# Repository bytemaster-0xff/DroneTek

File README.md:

# DroneTek
Collection of software, hardware and design resources for the Nivek Drone Family

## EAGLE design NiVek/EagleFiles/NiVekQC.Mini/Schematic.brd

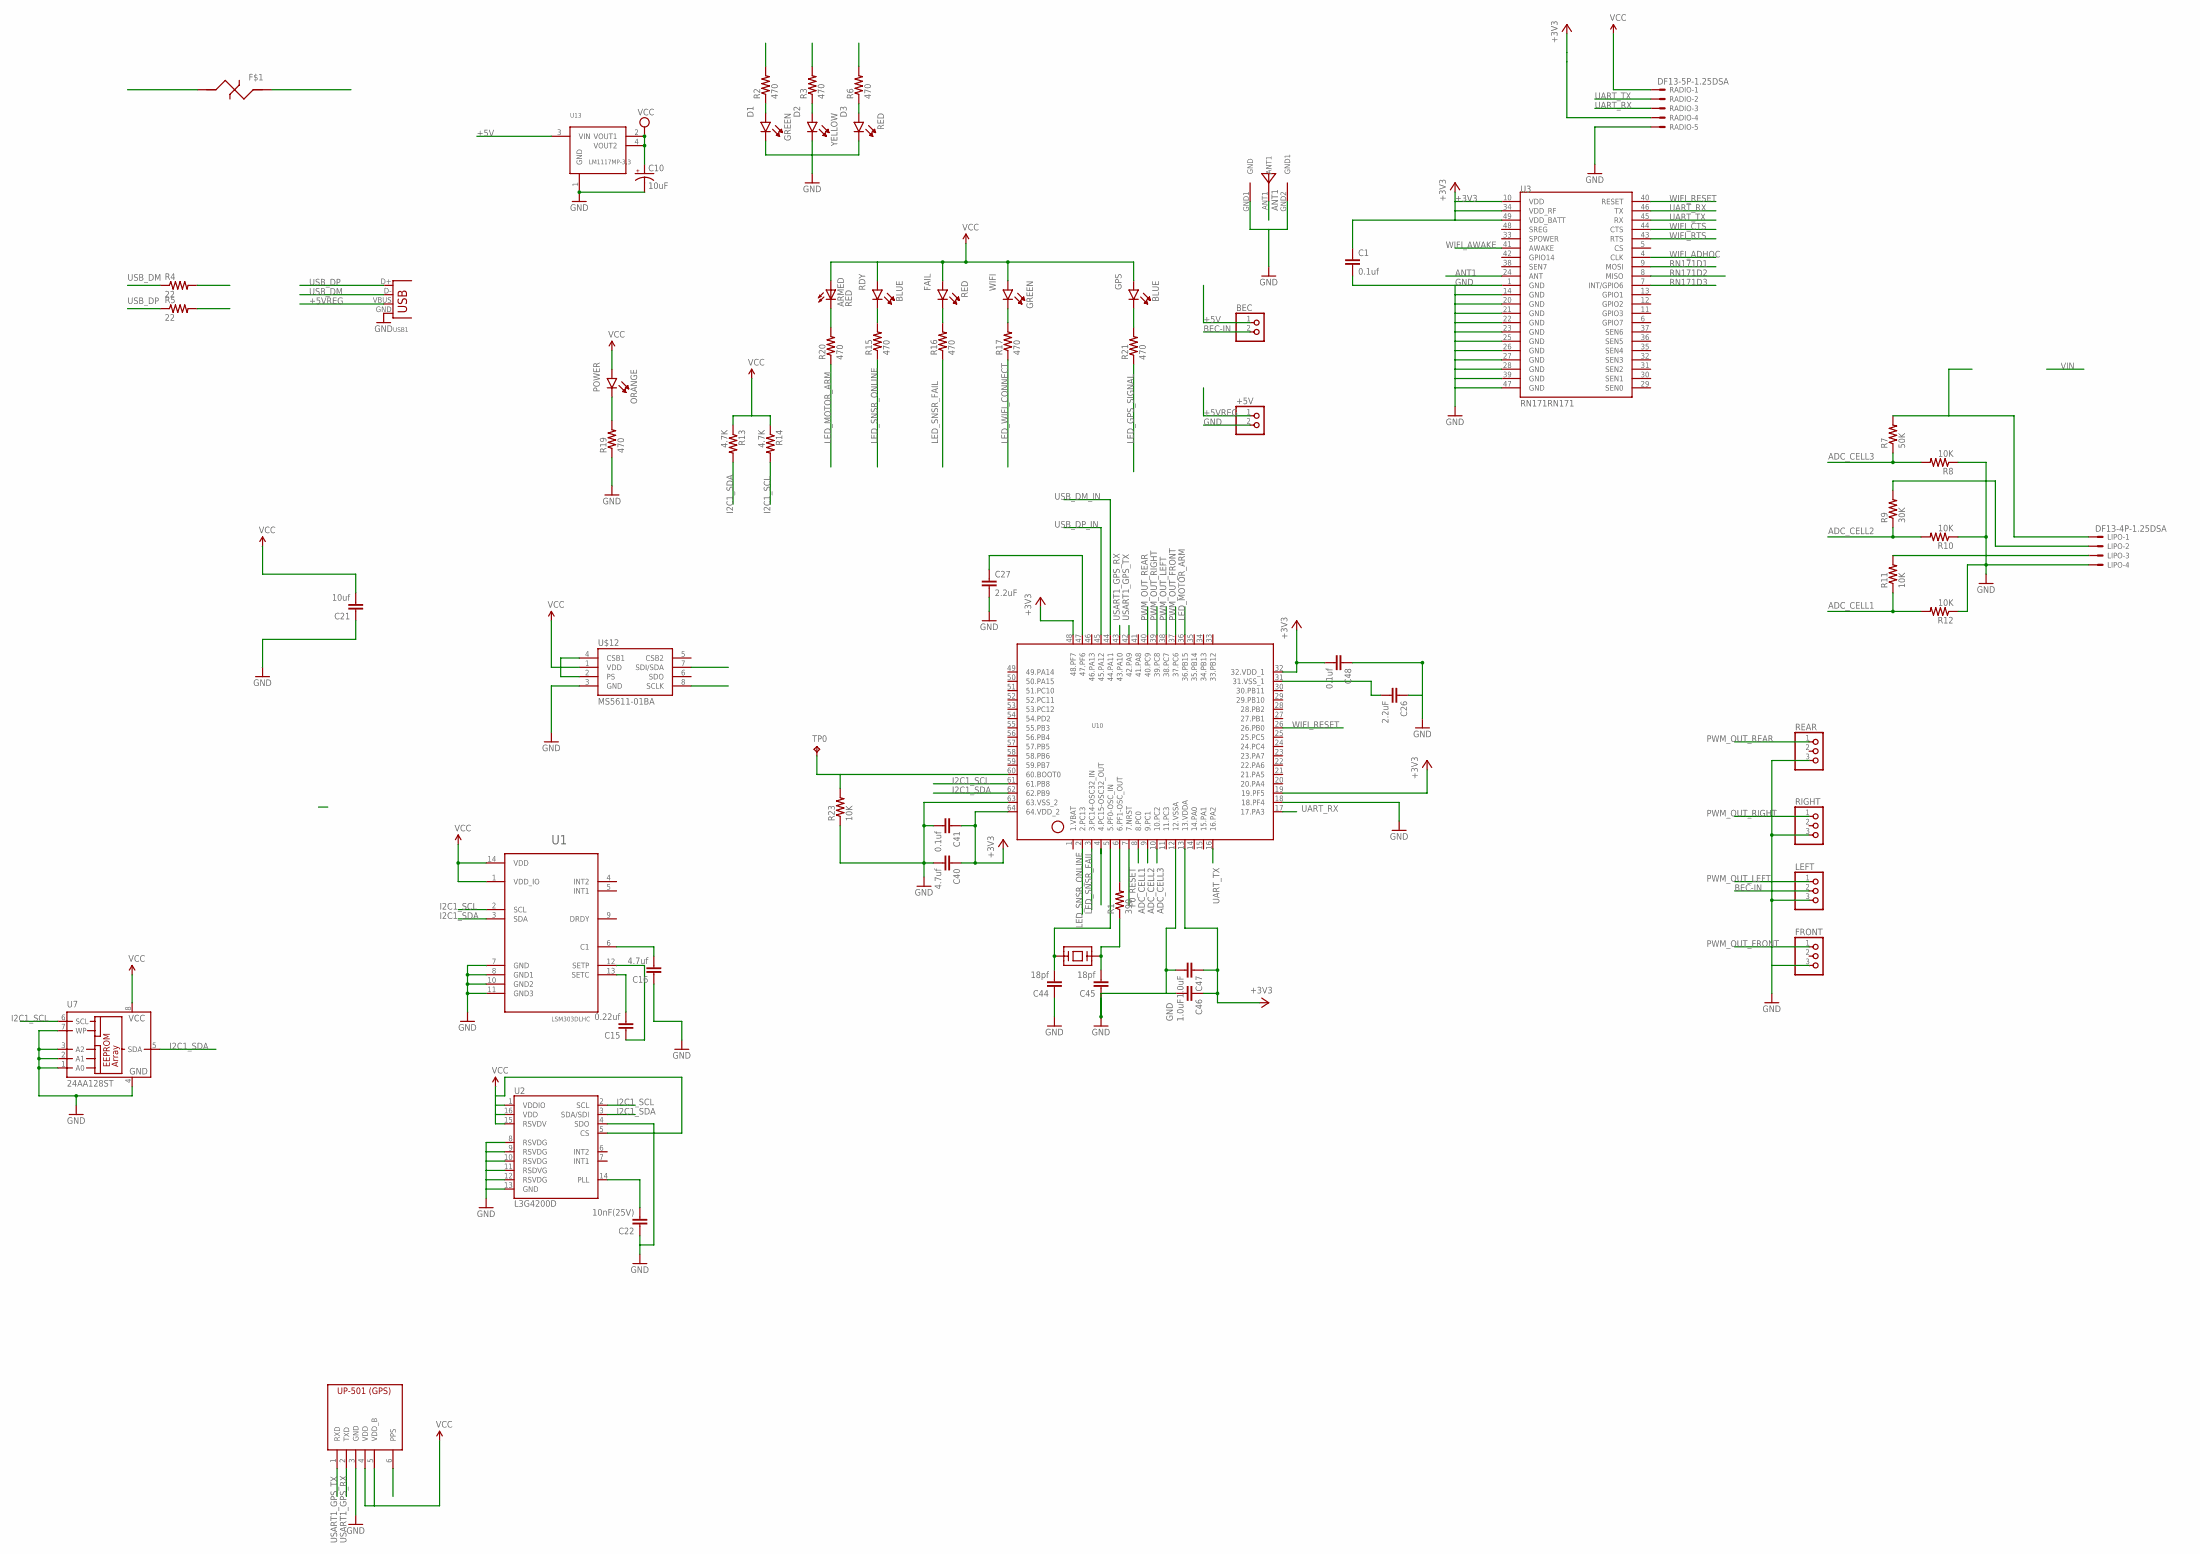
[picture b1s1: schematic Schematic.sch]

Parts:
+5V: PINHD-1X2; 1X02
ARMED: RED; LED-1206
BEC: PINHD-1X2; 1X02
C1, C41, C48: 0.1uf; 0805
C10: 10uF; CT3528
C15: 0.22uf; 0805
C16, C40: 4.7uf; 0805
C21: 10uf; 0805
C22: 10nF(25V); 0805
C26, C27: 2.2uF; 0805
C44, C45: 18pf; 0805
C46, C47: 1.0uF; 0805
D1: GREEN; LED0805
D2: YELLOW; LED0805
D3: RED; LED0805
F1: 1206L050_FUSE
FAIL: RED; LED0805
FRONT: PINHD-1X3; 1X03
GPS: BLUE; LED0805
LEFT: PINHD-1X3; 1X03
LIPO: DF13-4P-1.25DSA
POWER: ORANGE; LED0805
R1: 390; 0805
R2, R3, R6, R15, R16, R17, R19, R20, R21: 470; 0805
R4, R5: 22; 0805
R7: 50K; 0805
R8, R10, R11, R12, R23: 10K; 0805
R9: 30K; 0805
R13, R14: 4.7K; 0805
RADIO: DF13-5P-1.25DSA
RDY: BLUE; LED0805
REAR: PINHD-1X3; 1X03
RIGHT: PINHD-1X3; 1X03
TP0: TPTP15R; TP15R
U1: LSM303DLHC; LGA3X5X1-14L
U2: L3G4200D; LGA16-4X4
U3: RN171RN171; RN171
U7: 24AA128ST; TSSOP8; MPN 24AA128-I/ST
U10: STM32F051XXX; STM32F051XXX_LPFP64
U13: LM1117MP-3.3; SOT223
U$1: U.FLCONNECTOR
U$4: UP501; UP-501
U$12: MS5611-01BA
USB1: DX2R005HN2E700; USB-MB-S
WIFI: GREEN; LED0805
X2: ABRACON_ABM7; ABRACON_ABM7_CERAMIC_XTAL

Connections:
+3V3: ARMED.A, C1.1, C10.+, C21.2, C40.1, C41.1, C46.1, C47.1, C48.2, FAIL.P$1 (A), GPS.P$1 (A), POWER.P$1 (A), R13.1, R14.1, RADIO.4, RDY.P$1 (A), U1.1 (VDD_IO), U1.14 (VDD), U2.1 (VDDIO), U2.5 (CS), U2.15 (RSVDV), U2.16 (VDD), U3.10 (VDD), U3.34 (VDD_RF), U3.49 (VDD_BATT), U7.8 (VCC), U10.13 (13.VDDA), U10.19 (19.PF5), U10.32 (32.VDD_1), U10.48 (48.PF7), U10.64 (64.VDD_2), U13.2 (VOUT1), U13.4 (VOUT2), U$4.4 (VDD), U$4.5 (VDD_B), U$12.1 (VDD), U$12.2 (PS), U$12.4 (CSB1), WIFI.P$1 (A)
+5V: BEC.1, F1.P$2, RADIO.1, U13.3 (VIN)
+5VREG: +5V.1, F1.P$1, USB1.VBUS
ADC_CELL1: R11.1, R12.2, U10.8 (8.PC0)
ADC_CELL2: R9.1, R10.2, U10.9 (9.PC1)
ADC_CELL3: R7.1, R8.2, U10.10 (10.PC2)
ANT1: U3.24 (ANT), U$1.ANT1
BEC-IN: BEC.2, LEFT.2
F0_RESET: U10.7 (7.NRST)
GND: +5V.2, C1.2, C10.-, C16.1, C21.1, C22.1, C26.1, C27.2, C40.2, C41.2, C44.1, C45.1, C46.2, C47.2, C48.1, D1.C, D2.C, D3.C, FRONT.3, LEFT.3, LIPO.4, R8.1, R10.1, R12.1, R19.1, R23.1, RADIO.5, REAR.3, RIGHT.3, U1.7 (GND), U1.8 (GND1), U1.10 (GND2), U1.11 (GND3), U2.4 (SDO), U2.8 (RSVDG), U2.9 (RSVDG), U2.10 (RSVDG), U2.11 (RSDVG), U2.12 (RSVDG), U2.13 (GND), U3.1 (GND), U3.14 (GND), U3.20 (GND), U3.21 (GND), U3.22 (GND), U3.23 (GND), U3.25 (GND), U3.26 (GND), U3.27 (GND), U3.28 (GND), U3.39 (GND), U3.47 (GND), U7.1 (A0), U7.2 (A1), U7.3 (A2), U7.4 (GND), U7.7 (WP), U10.12 (12.VSSA), U10.18 (18.PF4), U10.63 (63.VSS_2), U13.1 (GND), U$1.GND1 (GND), U$1.GND2 (GND1), U$4.3 (GND), U$12.3 (GND), USB1.GND
I2C1_SCL: R14.2, U1.2 (SCL), U2.2 (SCL), U7.6 (SCL), U10.61 (61.PB8), U$12.8 (SCLK)
I2C1_SDA: R13.2, U1.3 (SDA), U2.3 (SDA/SDI), U7.5 (SDA), U10.62 (62.PB9), U$12.7 (SDI/SDA)
LED_GPS_SIGNAL: R21.1, U$4.6 (PPS)
LED_MOTOR_ARM: R20.1, U10.36 (36.PB15)
LED_SNSR_FAIL: R16.1, U10.3 (3.PC14-OSC32_IN)
LED_SNSR_ONLINE: R15.1, U10.2 (2.PC13)
LED_WIFI_CONNECT: R17.1, U10.4 (4.PC15-OSC32_OUT)
unnamed: D1.P$1 (A), R2.1
unnamed: D2.P$1 (A), R3.1
unnamed: R1.2, U10.6 (6.PF1-OSC_OUT)
unnamed: D3.P$1 (A), R6.1
unnamed: C16.2, U1.6 (C1)
unnamed: R15.2, RDY.C
unnamed: C15.1, U1.12 (SETP)
unnamed: C15.2, U1.13 (SETC)
unnamed: FAIL.C, R16.2
unnamed: ARMED.C, R20.2
unnamed: LIPO.3, R11.2
unnamed: LIPO.2, R9.2
unnamed: R17.2, WIFI.C
unnamed: POWER.C, R19.2
unnamed: R23.2, TP0.TP, U10.60 (60.BOOT0)
unnamed: C22.2, U2.14 (PLL)
unnamed: GPS.C, R21.2
unnamed: C26.2, U10.31 (31.VSS_1)
unnamed: C27.1, U10.47 (47.PF6)
OSC_IN: C44.2, U10.5 (5.PF0-OSC_IN), X2.P$1
OSC_OUT: C45.2, R1.1, X2.P$2
PWM_OUT_FRONT: FRONT.1, U10.37 (37.PC6)
PWM_OUT_LEFT: LEFT.1, U10.38 (38.PC7)
PWM_OUT_REAR: REAR.1, U10.40 (40.PC9)
PWM_OUT_RIGHT: RIGHT.1, U10.39 (39.PC8)
RN171D1: R2.2, U3.9 (MOSI)
RN171D2: R3.2, U3.8 (MISO)
RN171D3: R6.2, U3.7 (INT/GPIO6)
UART_RX: RADIO.3, U3.46 (TX), U10.17 (17.PA3)
UART_TX: RADIO.2, U3.45 (RX), U10.16 (16.PA2)
USART1_GPS_RX: U10.43 (43.PA10), U$4.2 (TXD)
USART1_GPS_TX: U10.42 (42.PA9), U$4.1 (RXD)
USB_DM: R4.1, USB1.D-
USB_DM_IN: R4.2, U10.44 (44.PA11)
USB_DP: R5.1, USB1.D+
USB_DP_IN: R5.2, U10.45 (45.PA12)
VIN_PROTECTED: LIPO.1, R7.2
WIFI_ADHOC: U3.4 (CLK)
WIFI_AWAKE: U3.41 (AWAKE)
WIFI_CTS: U3.44 (CTS)
WIFI_RESET: U3.40 (RESET), U10.26 (26.PB0)
WIFI_RTS: U3.43 (RTS)

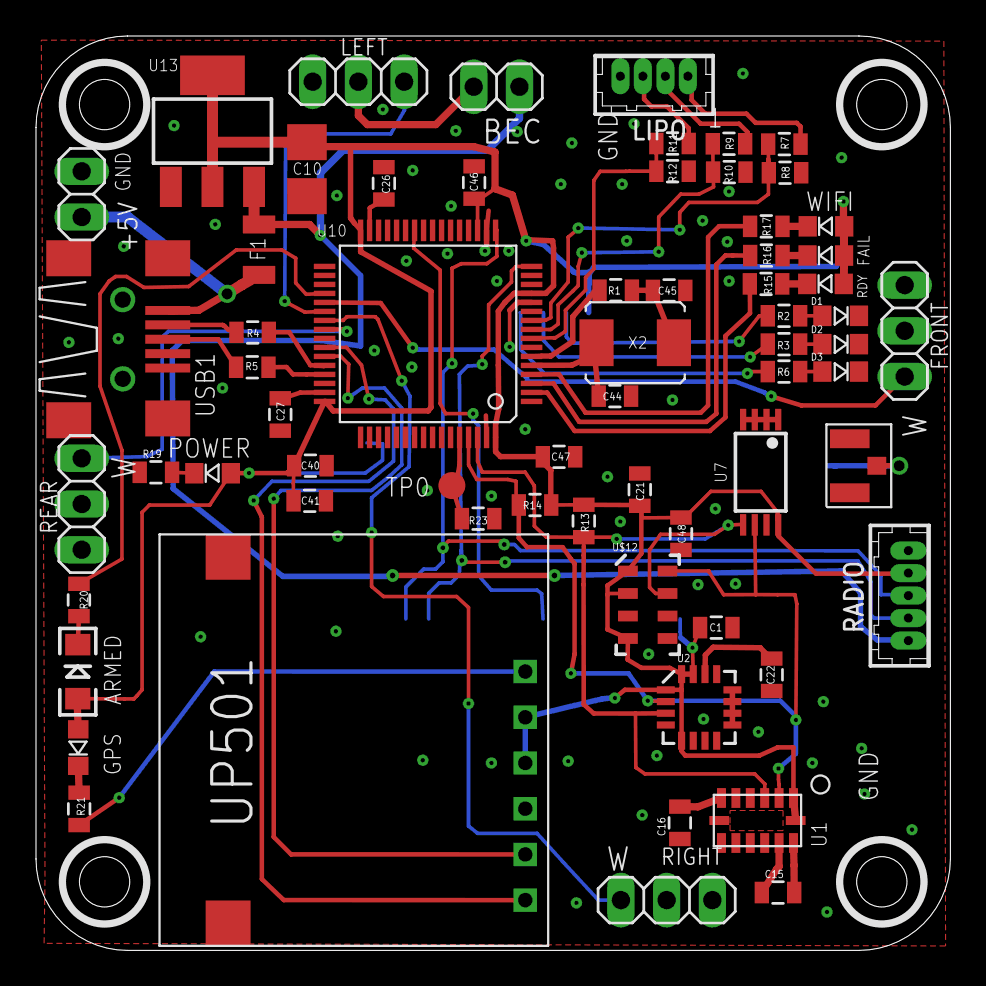
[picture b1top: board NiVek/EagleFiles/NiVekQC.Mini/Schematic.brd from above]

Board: 2 copper layers, 50.8 x 50.8 mm, 66 parts (1 on the bottom side), 54 nets.

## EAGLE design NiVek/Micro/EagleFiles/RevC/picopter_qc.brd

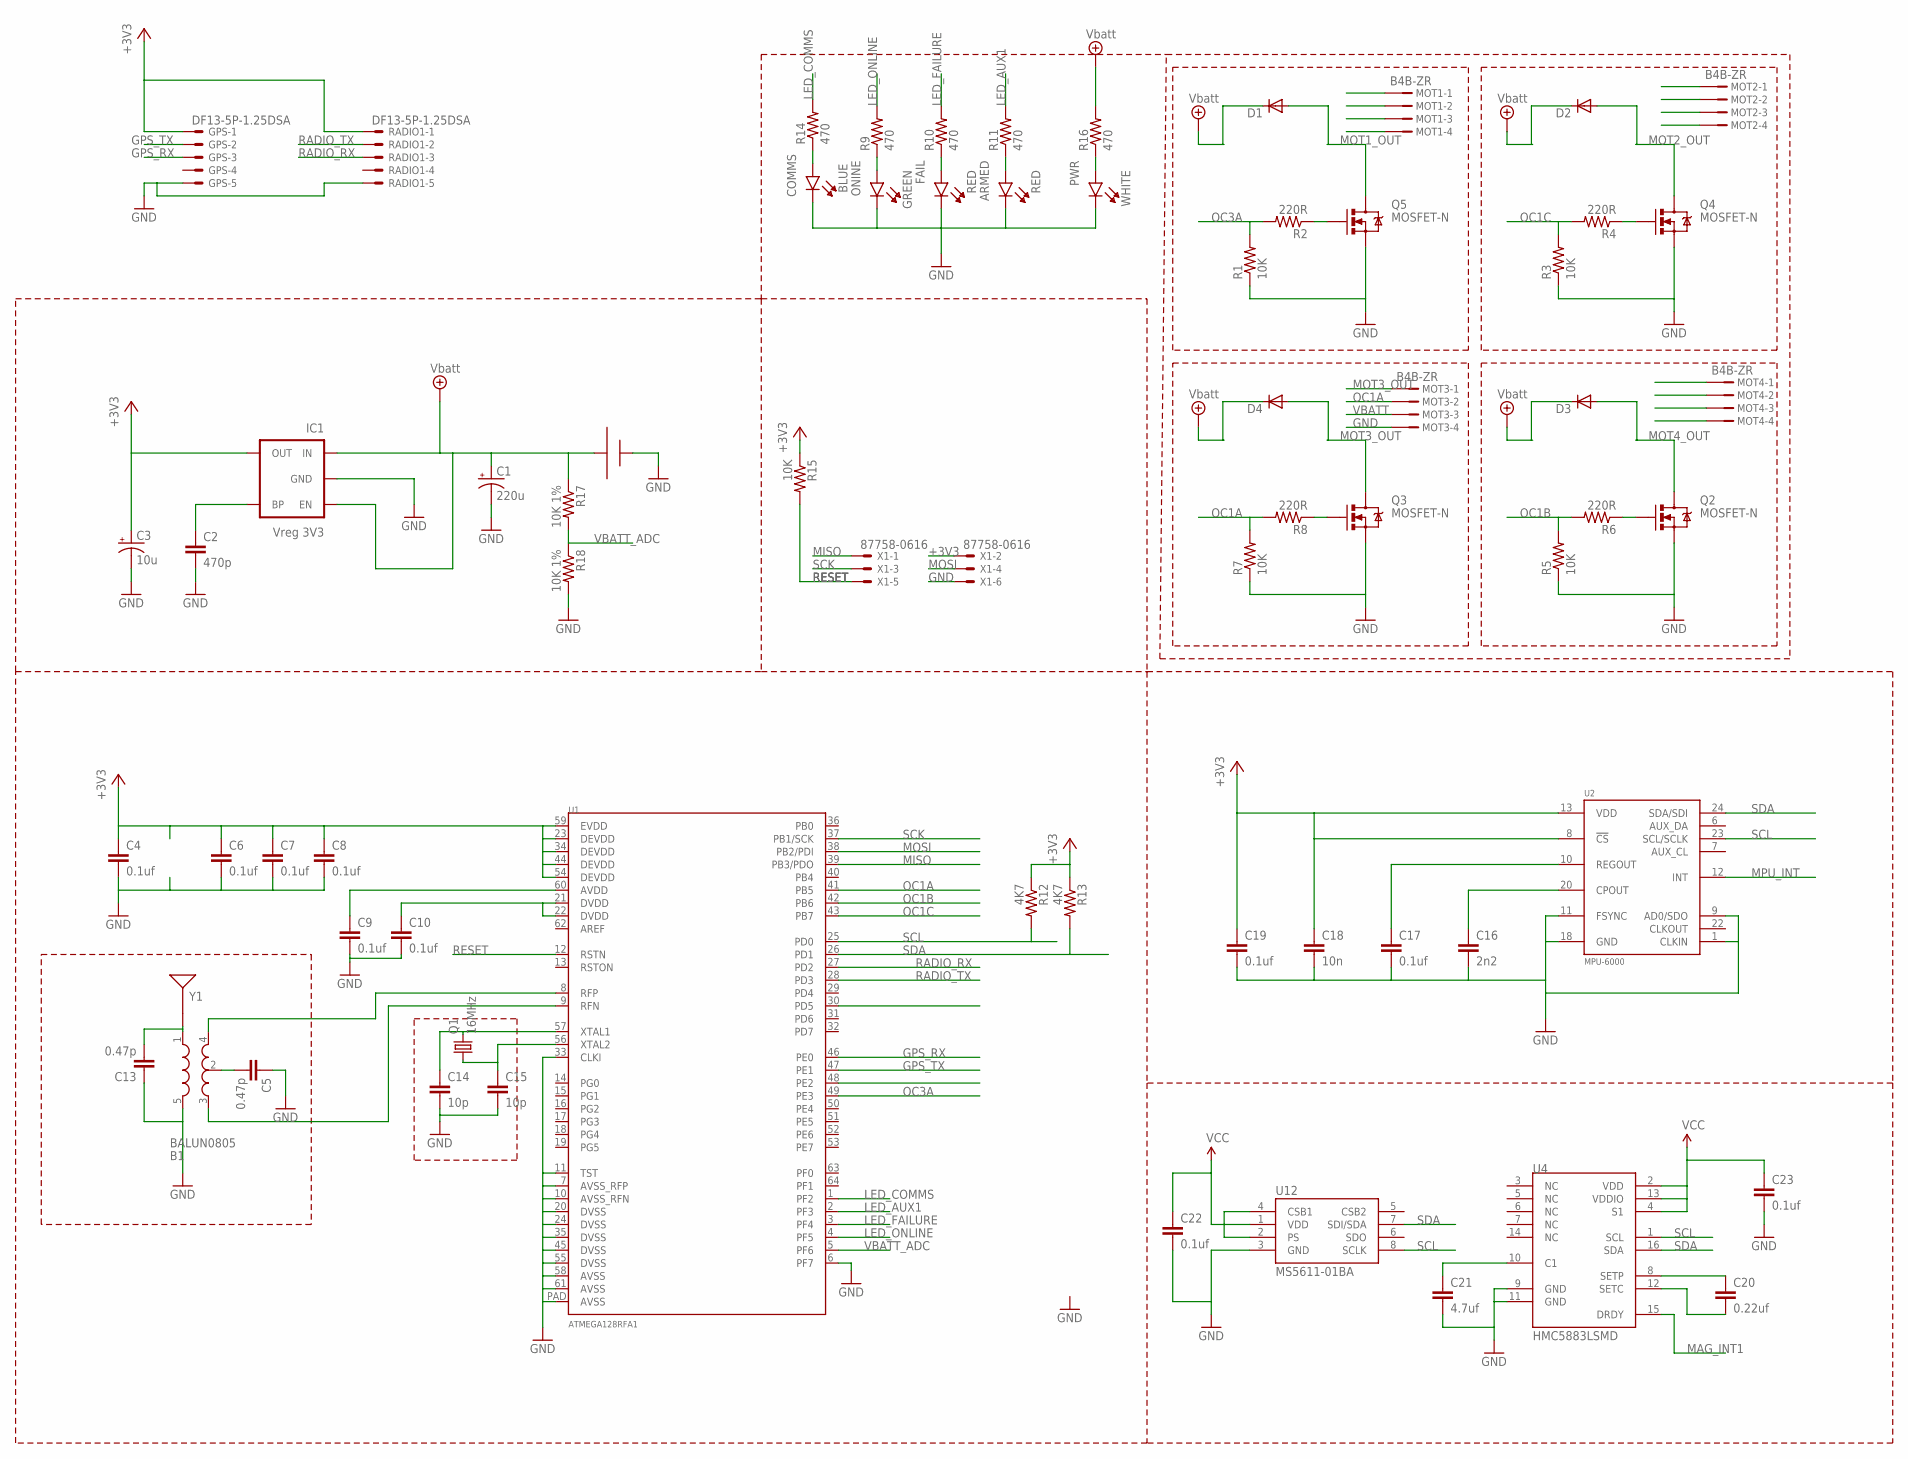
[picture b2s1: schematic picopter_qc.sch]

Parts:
ARMED: RED; LED0805
B1: BALUN0805; BALUN
BATT1: BATT-CONNJST-PH-VERT; JST-PH-2-VERT
C1: 220u; SMC_B
C2: 470p; C0603
C3: 10u; SMC_B
C4, C6, C7, C8, C9, C10, C17, C19, C22, C23: 0.1uf; C0603
C5, C13: 0.47p; C0603
C14, C15: 10p; C0603
C16: 2n2; C0603
C18: 10n; C0603
C20: 0.22uf; C0603
C21: 4.7uf; C0603
COMMS: BLUE; LED0805
D1, D2, D3, D4: DIODE-MINIMELF; MINIMELF
FAIL: RED; LED0805
GPS: DF13-5P-1.25DSA
IC1: Vreg 3V3; SOT23-5
MOT1, MOT2, MOT3, MOT4: B4B-ZR
ONINE: GREEN; LED0805
PWR: WHITE; LED0805
Q1: 16MHz; CTS406
Q2, Q3, Q4, Q5: MOSFET-N; SOT23-3
R1, R3, R5, R7, R15: 10K; R0603
R2, R4, R6, R8: 220R; R0603
R9, R10, R11, R14, R16: 470; 0805
R12, R13: 4K7; R0603
R17, R18: 10K 1%; R0603
RADIO1: DF13-5P-1.25DSA
U1: ATMEGA128RFA1; QFN-64
U2: MPU-6000; QFN-24
U4: HMC5883LSMD; 16LPCC
U12: MS5611-01BA
X1: 87758-0616
Y1: ANTENNA2SMD5; ANTENNA-CHIP5

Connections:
+3V3: C3.+, C4.1, C6.1, C7.1, C8.1, C18.1, C19.1, C22.1, C23.1, GPS.1, IC1.5 (OUT), R12.1, R13.1, R15.1, RADIO1.1, U1.23 (DEVDD), U1.34 (DEVDD), U1.44 (DEVDD), U1.54 (DEVDD), U1.59 (EVDD), U2.8 (!CS), U2.13 (VDD), U4.2 (VDD), U4.4 (S1), U4.13 (VDDIO), U12.1 (VDD), U12.2 (PS), U12.4 (CSB1), X1.2
GND: ARMED.C, B1.5 (GND), BATT1.N, C1.-, C2.2, C3.-, C4.2, C5.1, C6.2, C7.2, C8.2, C9.2, C10.2, C13.1, C14.2, C15.2, C16.2, C17.2, C18.2, C19.2, C21.2, C22.2, C23.2, COMMS.C, FAIL.C, GPS.5, IC1.2 (GND), MOT1.4, MOT2.4, MOT3.4, MOT4.4, ONINE.C, PWR.C, Q2.2 (S), Q3.2 (S), Q4.2 (S), Q5.2 (S), R1.1, R3.1, R5.1, R7.1, R18.2, RADIO1.5, U1.6 (PF7), U1.7 (AVSS_RFP), U1.10 (AVSS_RFN), U1.11 (TST), U1.20 (DVSS), U1.24 (DVSS), U1.33 (CLKI), U1.35 (DVSS), U1.45 (DVSS), U1.55 (DVSS), U1.58 (AVSS), U1.61 (AVSS), U1.PAD (AVSS), U2.1 (CLKIN), U2.9 (AD0/SDO), U2.11 (FSYNC), U2.18 (GND), U4.9 (GND), U4.11 (GND), U12.3 (GND), X1.6
GPS_RX: GPS.3, U1.46 (PE0)
GPS_TX: GPS.2, U1.47 (PE1)
LED_AUX1: R11.2, U1.2 (PF3)
LED_COMMS: R14.2, U1.1 (PF2)
LED_FAILURE: R10.2, U1.3 (PF4)
LED_ONLINE: R9.2, U1.4 (PF5)
MAG_INT1: U1.48 (PE2), U4.15 (DRDY)
MISO: U1.39 (PB3/PDO), X1.1
MOSI: U1.38 (PB2/PDI), X1.4
MOT1_OUT: D1.A, MOT1.1, Q5.3 (D)
MOT2_OUT: D2.A, MOT2.1, Q4.3 (D)
MOT3_OUT: D4.A, MOT3.1, Q3.3 (D)
MOT4_OUT: D3.A, MOT4.1, Q2.3 (D)
MPU_INT: U1.30 (PD5), U2.12 (INT)
MS1: B1.1 (IN), C13.2, Y1.FEED
unnamed: C2.1, IC1.4 (BP)
unnamed: B1.2 (GND), C5.2
unnamed: C10.1, U1.21 (DVDD), U1.22 (DVDD)
unnamed: C9.1, U1.60 (AVDD)
unnamed: B1.3 (OUT1), U1.9 (RFN)
unnamed: B1.4 (OUT2), U1.8 (RFP)
unnamed: C14.1, Q1.3 (2), U1.57 (XTAL1)
unnamed: C15.1, Q1.1, U1.56 (XTAL2)
unnamed: ONINE.P$1 (A), R9.1
unnamed: FAIL.P$1 (A), R10.1
unnamed: C20.1, U4.8 (SETP)
unnamed: C16.1, U2.20 (CPOUT)
unnamed: C17.1, U2.10 (REGOUT)
unnamed: C20.2, U4.12 (SETC)
unnamed: C21.1, U4.10 (C1)
unnamed: ARMED.P$1 (A), R11.1
unnamed: COMMS.P$1 (A), R14.1
unnamed: PWR.P$1 (A), R16.1
unnamed: Q5.1 (G), R2.1
unnamed: Q4.1 (G), R4.1
unnamed: Q2.1 (G), R6.1
unnamed: Q3.1 (G), R8.1
OC1A: MOT3.2, R7.2, R8.2, U1.41 (PB5)
OC1B: MOT4.2, R5.2, R6.2, U1.42 (PB6)
OC1C: MOT2.2, R3.2, R4.2, U1.43 (PB7)
OC3A: MOT1.2, R1.2, R2.2, U1.49 (PE3)
RADIO_RX: RADIO1.3, U1.27 (PD2)
RADIO_TX: RADIO1.2, U1.28 (PD3)
RESET: R15.2, U1.12 (RSTN), X1.5
SCK: U1.37 (PB1/SCK), X1.3
SCL: R12.2, U1.25 (PD0), U2.23 (SCL/SCLK), U4.1 (SCL), U12.8 (SCLK)
SDA: R13.2, U1.26 (PD1), U2.24 (SDA/SDI), U4.16 (SDA), U12.7 (SDI/SDA)
VBATT: BATT1.P, C1.+, D1.C, D2.C, D3.C, D4.C, IC1.1 (IN), IC1.3 (EN), MOT1.3, MOT2.3, MOT3.3, MOT4.3, R16.2, R17.1
VBATT_ADC: R17.2, R18.1, U1.5 (PF6)

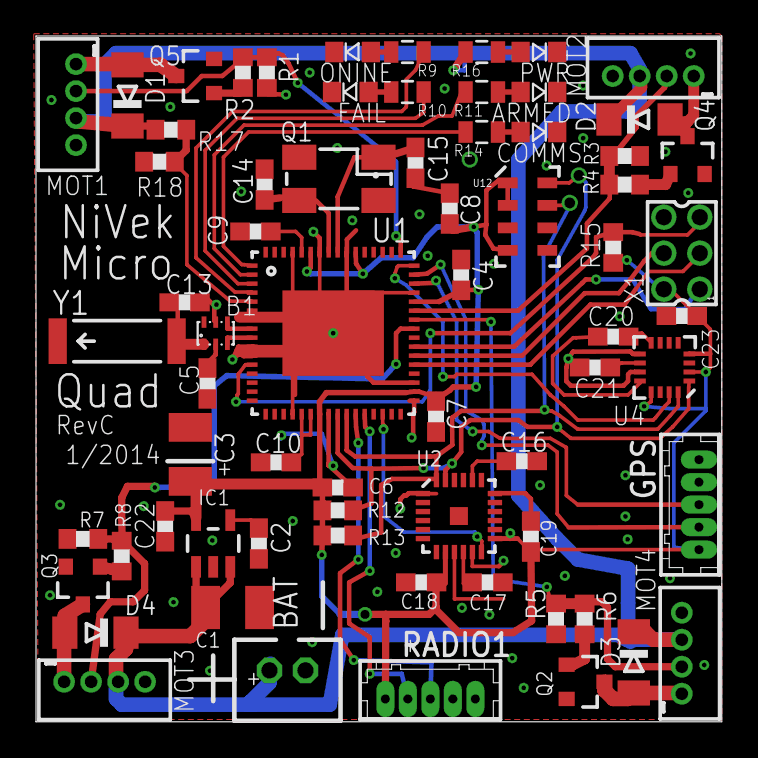
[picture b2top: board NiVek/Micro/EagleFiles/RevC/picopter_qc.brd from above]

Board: 2 copper layers, 38.1 x 38.1 mm, 68 parts (0 on the bottom side), 51 nets.

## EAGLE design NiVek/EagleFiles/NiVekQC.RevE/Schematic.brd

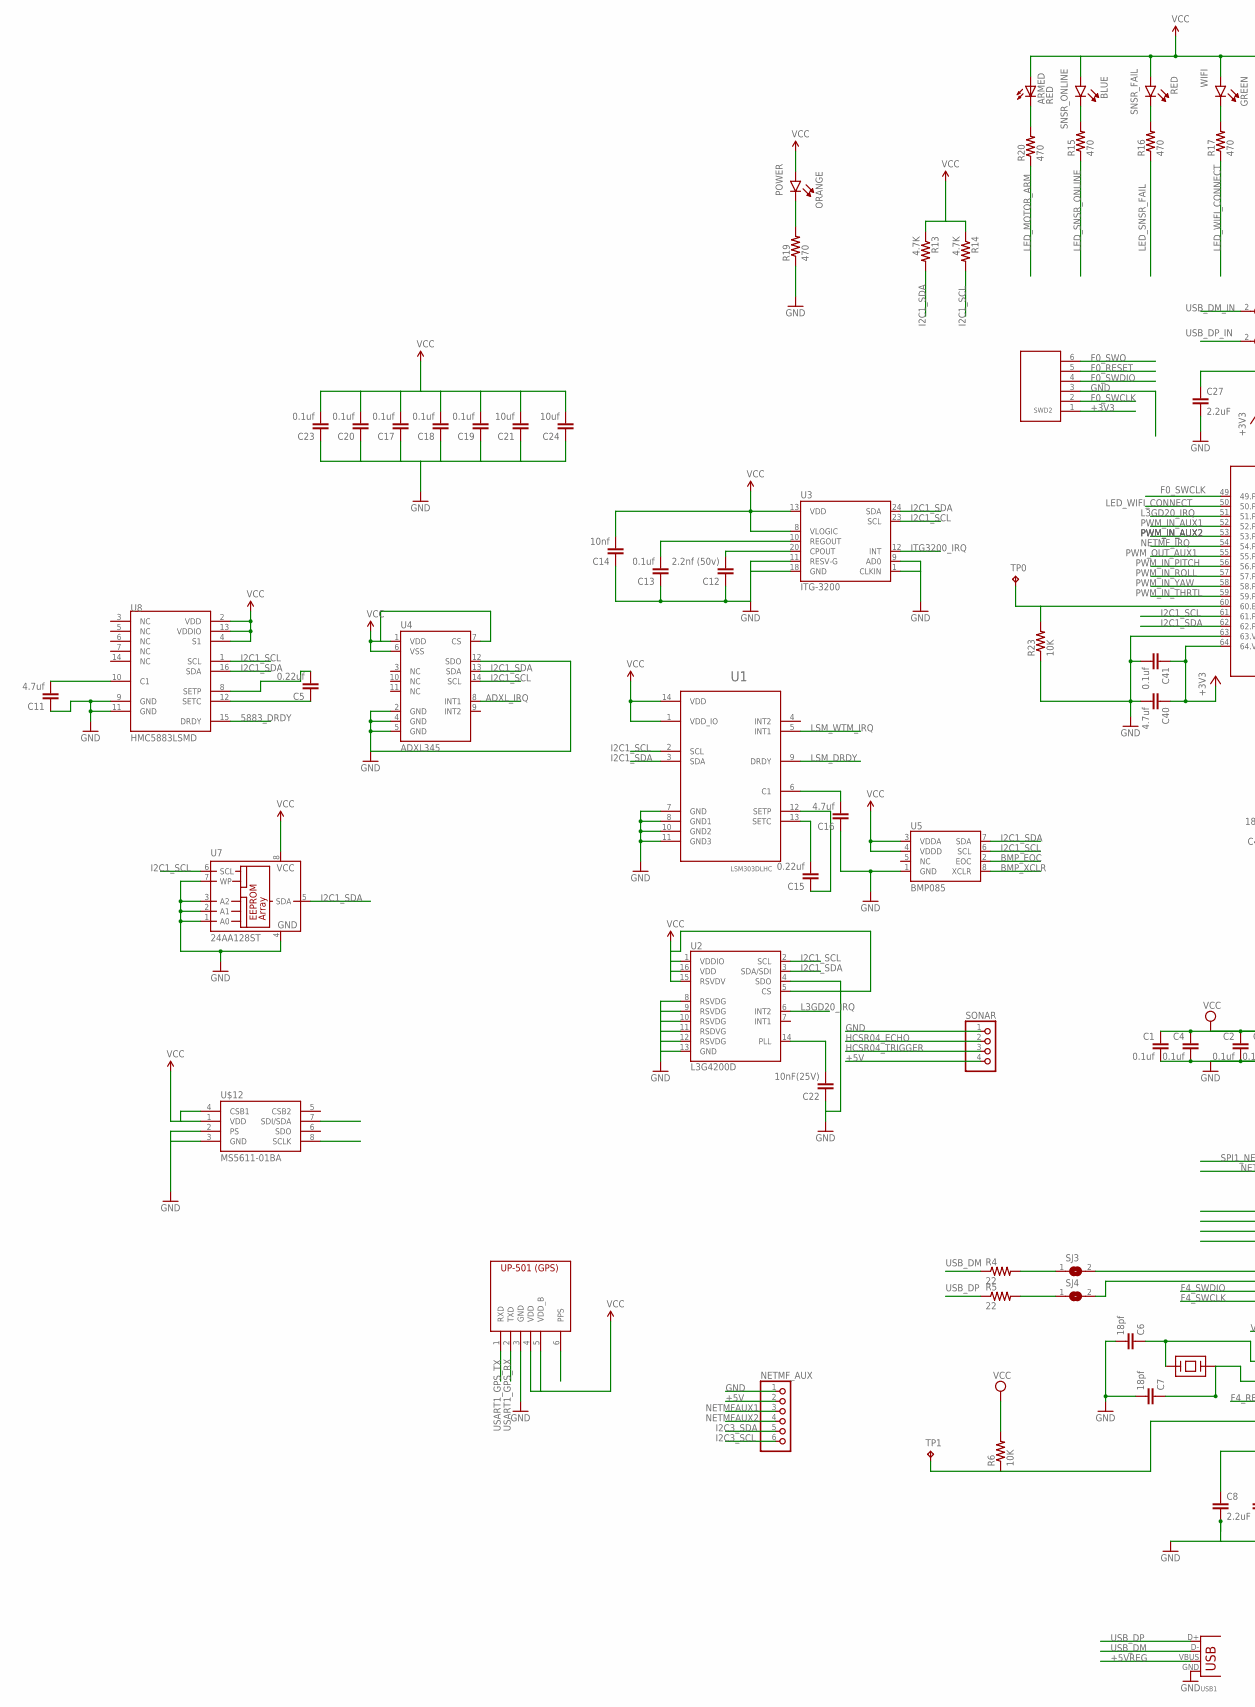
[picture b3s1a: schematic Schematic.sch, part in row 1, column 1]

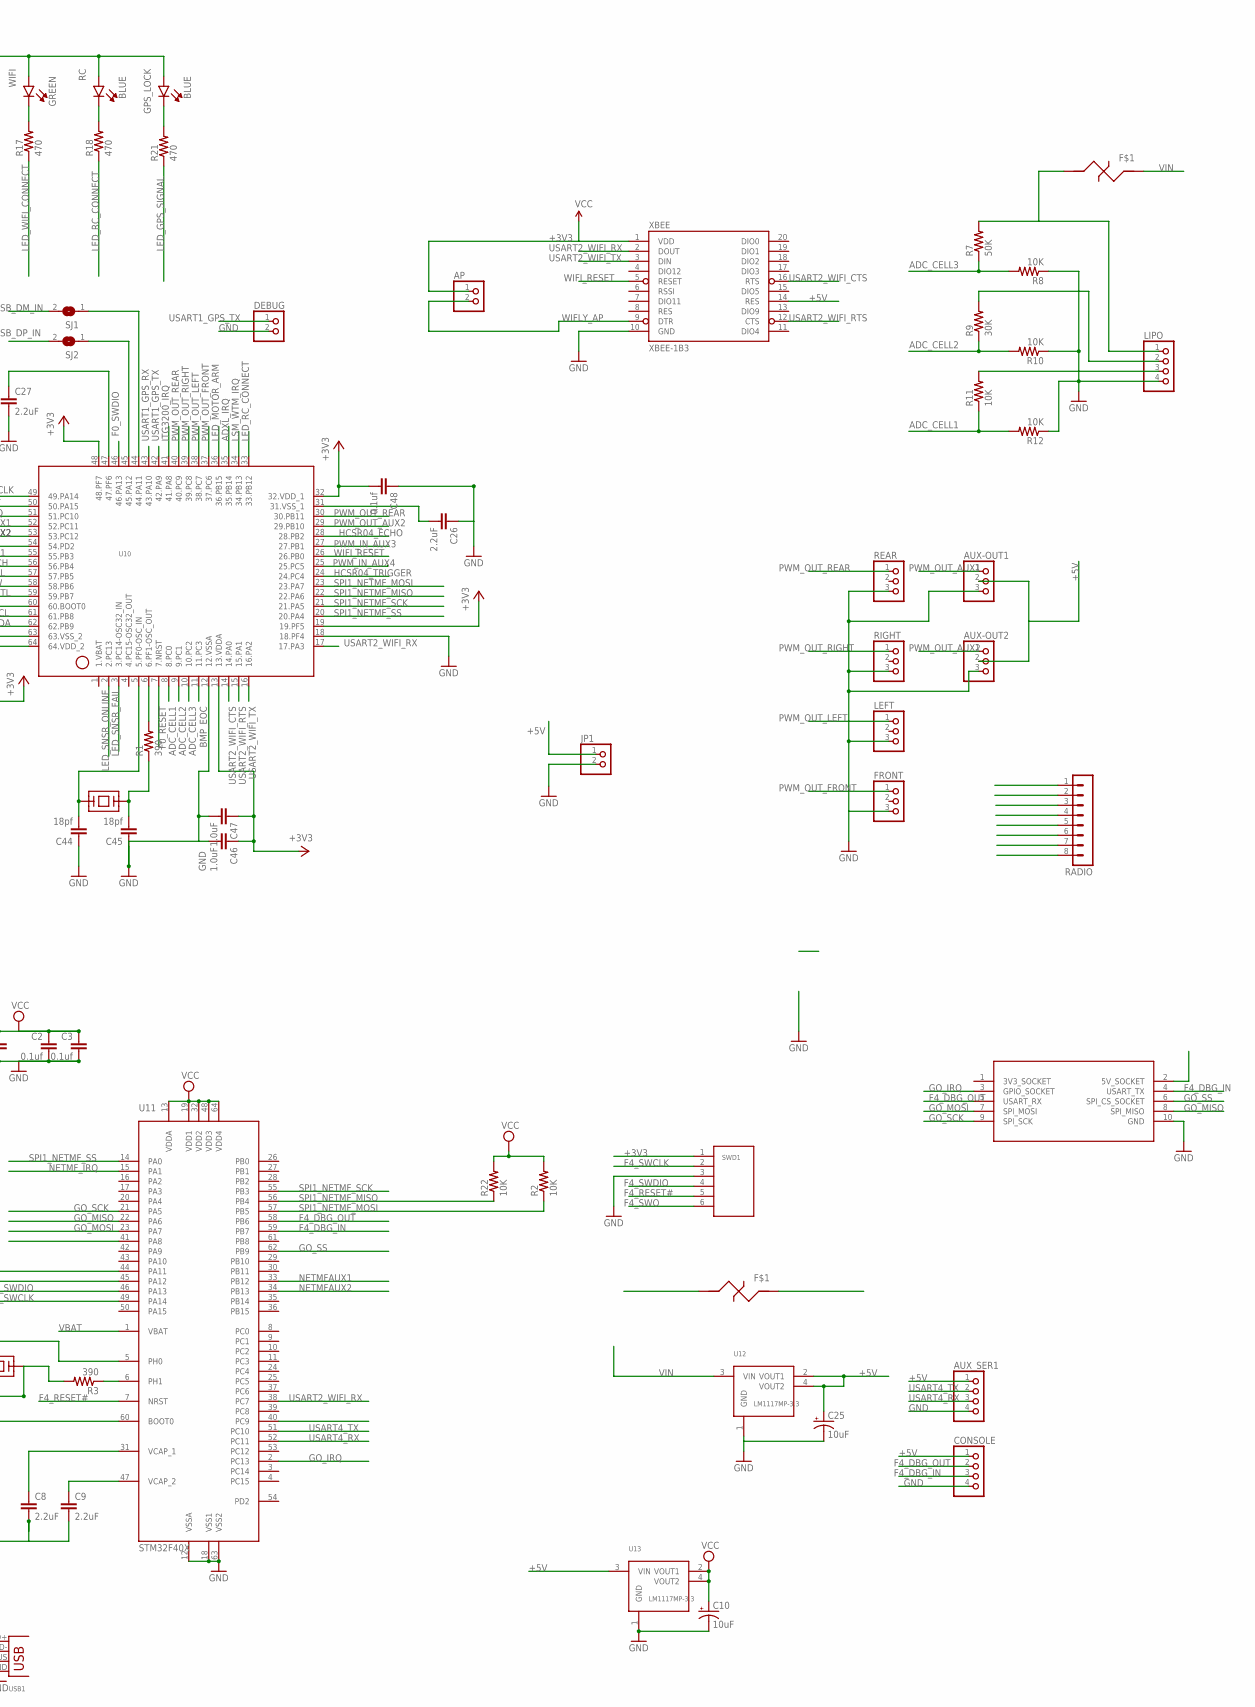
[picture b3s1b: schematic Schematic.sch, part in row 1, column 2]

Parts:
AP: PINHD-1X2; 1X02
ARMED: RED; LED-1206
AUX-OUT1, AUX-OUT2: PINHD-1X3; 1X03
AUX_SER1: PINHD-1X4; 1X04
C1, C2, C3, C4, C13, C17, C18, C19, C20, C23, C41, C48: 0.1uf; 0805
C5, C15: 0.22uf; 0805
C6, C7, C44, C45: 18pf; 0805
C8, C9, C26, C27: 2.2uF; 0805
C10, C25: 10uF; CT3528
C11, C16, C40: 4.7uf; 0805
C12: 2.2nf (50v); 0805
C14: 10nf; 0805
C21, C24: 10uf; 0805
C22: 10nF(25V); 0805
C46, C47: 1.0uF; 0805
CONSOLE: PINHD-1X4; 1X04
DEBUG: PINHD-1X2; 1X02
F1, F2: 1206L050_FUSE
FRONT: PINHD-1X3; 1X03
GO_BUS: GO!BUS; PIN2ROW_0.05"
GPS_LOCK: BLUE; LED0805
JP1: PINHD-1X2; 1X02
LEFT: PINHD-1X3; 1X03
LIPO: PINHD-1X4; 1X04
NETMF_AUX: PINHD-1X6; 1X06
POWER: ORANGE; LED0805
R1, R3: 390; 0805
R2, R6, R8, R10, R11, R12, R22, R23: 10K; 0805
R4, R5: 22; 0805
R7: 50K; 0805
R9: 30K; 0805
R13, R14: 4.7K; 0805
R15, R16, R17, R18, R19, R20, R21: 470; 0805
RADIO: MA08-1
RC: BLUE; LED0805
REAR: PINHD-1X3; 1X03
RIGHT: PINHD-1X3; 1X03
SJ1, SJ2, SJ3, SJ4: SJ
SNSR_FAIL: RED; LED0805
SNSR_ONLINE: BLUE; LED0805
SONAR: PINHD-1X4; 1X04
SWD1: JST-6PIN; JSTX6
SWD2: SWD-STM32F0; JSTX6
TP0, TP1: TPTP15R; TP15R
U1: LSM303DLHC; LGA3X5X1-14L
U2: L3G4200D; LGA16-4X4
U3: ITG-3200; QFN-24
U4: ADXL345; LGA14
U5: BMP085
U7: 24AA128ST; TSSOP8; MPN 24AA128-I/ST
U8: HMC5883LSMD; 16LPCC
U10: STM32F051XXX; STM32F051XXX_LPFP64
U11: STM32F40X; LQFP64
U12, U13: LM1117MP-3.3; SOT223
U$4: UP501; UP-501
U$12: MS5611-01BA
USB1: DX2R005HN2E700; USB-MB-S
WIFI: GREEN; LED0805
X1, X2: ABRACON_ABM7; ABRACON_ABM7_CERAMIC_XTAL
XBEE: XBEE-1B3; XBEE-SMD

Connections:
3V3_SOCKET: GO_BUS.1 (3V3_SOCKET)
5883_DRDY: U8.15 (DRDY)
+3V3: AP.1, ARMED.A, C1.1, C2.1, C3.1, C4.1, C10.+, C14.2, C17.2, C18.2, C19.2, C20.2, C21.2, C23.2, C24.2, C40.1, C41.1, C46.1, C47.1, C48.2, GPS_LOCK.P$1 (A), POWER.P$1 (A), R2.2, R6.2, R13.1, R14.1, R22.2, RC.P$1 (A), SNSR_FAIL.P$1 (A), SNSR_ONLINE.P$1 (A), SWD1.1, SWD2.1, U1.1 (VDD_IO), U1.14 (VDD), U2.1 (VDDIO), U2.5 (CS), U2.15 (RSVDV), U2.16 (VDD), U3.8 (VLOGIC), U3.13 (VDD), U4.1 (VDD), U4.6 (VSS), U4.7 (CS), U5.3 (VDDA), U5.4 (VDDD), U7.8 (VCC), U8.2 (VDD), U8.4 (S1), U8.13 (VDDIO), U10.13 (13.VDDA), U10.19 (19.PF5), U10.32 (32.VDD_1), U10.48 (48.PF7), U10.64 (64.VDD_2), U11.13 (VDDA), U11.19 (VDD1), U11.32 (VDD2), U11.48 (VDD3), U11.64 (VDD4), U13.2 (VOUT1), U13.4 (VOUT2), U$4.4 (VDD), U$4.5 (VDD_B), U$12.1 (VDD), U$12.4 (CSB1), WIFI.P$1 (A), XBEE.1 (VDD)
+5V: AUX-OUT1.2, AUX-OUT2.2, AUX_SER1.1, C25.+, CONSOLE.1, F1.P$2, GO_BUS.2 (5V_SOCKET), JP1.1, NETMF_AUX.2, SONAR.4, U12.2 (VOUT1), U12.4 (VOUT2), U13.3 (VIN), XBEE.14 (RES)
+5VREG: F1.P$1, USB1.VBUS
ADC_CELL1: R11.1, R12.2, U10.8 (8.PC0)
ADC_CELL2: R9.1, R10.2, U10.9 (9.PC1)
ADC_CELL3: R7.1, R8.2, U10.10 (10.PC2)
ADXL_IRQ: U4.8 (INT1), U10.35 (35.PB14)
BMP_EOC: U5.2 (EOC), U10.11 (11.PC3)
BMP_XCLR: U5.8 (XCLR)
F0_RESET: SWD2.5, U10.7 (7.NRST)
F0_SWCLK: SWD2.2, U10.49 (49.PA14)
F0_SWDIO: SWD2.4, U10.46 (46.PA13)
F0_SWO: SWD2.6
F4_DBG_IN: CONSOLE.3, GO_BUS.4 (USART_TX), U11.59 (PB7)
F4_DBG_OUT: CONSOLE.2, GO_BUS.5 (USART_RX), U11.58 (PB6)
F4_RESET#: SWD1.5, U11.7 (NRST)
F4_SWCLK: SWD1.2, U11.49 (PA14)
F4_SWDIO: SWD1.4, U11.46 (PA13)
F4_SWO: SWD1.6
GND: AUX-OUT1.3, AUX-OUT2.3, AUX_SER1.4, C1.2, C2.2, C3.2, C4.2, C6.2, C7.2, C8.2, C9.2, C10.-, C11.1, C12.1, C13.1, C14.1, C16.1, C17.1, C18.1, C19.1, C20.1, C21.1, C22.1, C23.1, C24.1, C25.-, C26.1, C27.2, C40.2, C41.2, C44.1, C45.1, C46.2, C47.2, C48.1, CONSOLE.4, DEBUG.2, FRONT.3, GO_BUS.10 (GND), JP1.2, LEFT.3, LIPO.4, NETMF_AUX.1, R8.1, R10.1, R12.1, R19.1, R23.1, REAR.3, RIGHT.3, SONAR.1, SWD1.3, SWD2.3, U1.7 (GND), U1.8 (GND1), U1.10 (GND2), U1.11 (GND3), U2.4 (SDO), U2.8 (RSVDG), U2.9 (RSVDG), U2.10 (RSVDG), U2.11 (RSDVG), U2.12 (RSVDG), U2.13 (GND), U3.1 (CLKIN), U3.9 (AD0), U3.11 (RESV-G), U3.18 (GND), U4.2 (GND), U4.4 (GND), U4.5 (GND), U4.12 (SDO), U5.1 (GND), U7.1 (A0), U7.2 (A1), U7.3 (A2), U7.4 (GND), U7.7 (WP), U8.9 (GND), U8.11 (GND), U10.12 (12.VSSA), U10.18 (18.PF4), U10.63 (63.VSS_2), U11.12 (VSSA), U11.18 (VSS1), U11.63 (VSS2), U12.1 (GND), U13.1 (GND), U$4.3 (GND), U$12.2 (PS), U$12.3 (GND), USB1.GND, XBEE.10 (GND)
GO_IRQ: GO_BUS.3 (GPIO_SOCKET), U11.2 (PC13)
GO_MISO: GO_BUS.8 (SPI_MISO), U11.22 (PA6)
GO_MOSI: GO_BUS.7 (SPI_MOSI), U11.23 (PA7)
GO_SCK: GO_BUS.9 (SPI_SCK), U11.21 (PA5)
GO_SS: GO_BUS.6 (SPI_CS_SOCKET), U11.62 (PB9)
HCSR04_ECHO: SONAR.2, U10.28 (28.PB2)
HCSR04_TRIGGER: SONAR.3, U10.24 (24.PC4)
I2C1_SCL: R14.2, U1.2 (SCL), U2.2 (SCL), U3.23 (SCL), U4.14 (SCL), U5.6 (SCL), U7.6 (SCL), U8.1 (SCL), U10.61 (61.PB8), U$12.8 (SCLK)
I2C1_SDA: R13.2, U1.3 (SDA), U2.3 (SDA/SDI), U3.24 (SDA), U4.13 (SDA), U5.7 (SDA), U7.5 (SDA), U8.16 (SDA), U10.62 (62.PB9), U$12.7 (SDI/SDA)
I2C3_SCL: NETMF_AUX.6, U11.41 (PA8)
I2C3_SDA: NETMF_AUX.5, U11.40 (PC9)
ITG3200_IRQ: U3.12 (INT), U10.41 (41.PA8)
L3GD20_IRQ: U2.6 (INT2), U10.51 (51.PC10)
LED_GPS_SIGNAL: R21.1, U$4.6 (PPS)
LED_MOTOR_ARM: R20.1, U10.36 (36.PB15)
LED_RC_CONNECT: R18.1, U10.33 (33.PB12)
LED_SNSR_FAIL: R16.1, U10.3 (3.PC14-OSC32_IN)
LED_SNSR_ONLINE: R15.1, U10.2 (2.PC13)
LED_WIFI_CONNECT: R17.1, U10.50 (50.PA15)
LSM_DRDY: U1.9 (DRDY)
LSM_WTM_IRQ: U1.5 (INT1), U10.34 (34.PB13)
unnamed: C5.1, U8.12 (SETC)
unnamed: C9.1, U11.47 (VCAP_2)
unnamed: C8.1, U11.31 (VCAP_1)
unnamed: C5.2, U8.8 (SETP)
unnamed: R1.2, U10.6 (6.PF1-OSC_OUT)
unnamed: R3.1, U11.6 (PH1)
unnamed: C11.2, U8.10 (C1)
unnamed: C16.2, U1.6 (C1)
unnamed: R15.2, SNSR_ONLINE.C
unnamed: C12.2, U3.20 (CPOUT)
unnamed: C13.2, U3.10 (REGOUT)
unnamed: C15.1, U1.12 (SETP)
unnamed: C15.2, U1.13 (SETC)
unnamed: R16.2, SNSR_FAIL.C
unnamed: ARMED.C, R20.2
unnamed: LIPO.3, R11.2
unnamed: LIPO.2, R9.2
unnamed: R6.1, TP1.TP, U11.60 (BOOT0)
unnamed: R17.2, WIFI.C
unnamed: R18.2, RC.C
unnamed: POWER.C, R19.2
unnamed: R23.2, TP0.TP, U10.60 (60.BOOT0)
unnamed: C22.2, U2.14 (PLL)
unnamed: GPS_LOCK.C, R21.2
unnamed: C26.2, U10.31 (31.VSS_1)
unnamed: C27.1, U10.47 (47.PF6)
NETMFAUX1: NETMF_AUX.3, U11.33 (PB12)
NETMFAUX2: NETMF_AUX.4, U11.34 (PB13)
NETMF_IRQ: U10.54 (54.PD2), U11.15 (PA1)
OSC_IN: C44.2, U10.5 (5.PF0-OSC_IN), X2.P$1
OSC_OUT: C45.2, R1.1, X2.P$2
PWM_IN_AUX1: RADIO.5, U10.52 (52.PC11)
PWM_IN_AUX2: RADIO.6, U10.53 (53.PC12)
PWM_IN_AUX3: RADIO.7, U10.27 (27.PB1)
PWM_IN_AUX4: RADIO.8, U10.25 (25.PC5)
PWM_IN_PITCH: RADIO.1, U10.56 (56.PB4)
PWM_IN_ROLL: RADIO.2, U10.57 (57.PB5)
PWM_IN_THRTL: RADIO.3, U10.59 (59.PB7)
PWM_IN_YAW: RADIO.4, U10.58 (58.PB6)
PWM_OUT_AUX1: AUX-OUT1.1, U10.55 (55.PB3)
PWM_OUT_AUX2: AUX-OUT2.1, U10.29 (29.PB10)
PWM_OUT_FRONT: FRONT.1, U10.37 (37.PC6)
PWM_OUT_LEFT: LEFT.1, U10.38 (38.PC7)
PWM_OUT_REAR: REAR.1, U10.30 (30.PB11), U10.40 (40.PC9)
PWM_OUT_RIGHT: RIGHT.1, U10.39 (39.PC8)
SPI1_NETMF_MISO: R22.1, U10.22 (22.PA6), U11.56 (PB4)
SPI1_NETMF_MOSI: R2.1, U10.23 (23.PA7), U11.57 (PB5)
SPI1_NETMF_SCK: U10.21 (21.PA5), U11.55 (PB3)
SPI1_NETMF_SS: U10.20 (20.PA4), U11.14 (PA0)
USART1_GPS_RX: U10.43 (43.PA10), U$4.2 (TXD)
USART1_GPS_TX: DEBUG.1, U10.42 (42.PA9), U$4.1 (RXD)
USART2_WIFI_CTS: U10.14 (14.PA0), XBEE.16 (RTS)
USART2_WIFI_RTS: U10.15 (15.PA1), XBEE.12 (CTS)
USART2_WIFI_RX: U10.17 (17.PA3), U11.38 (PC7), XBEE.2 (DOUT)
USART2_WIFI_TX: U10.16 (16.PA2), XBEE.3 (DIN)
USART4_RX: AUX_SER1.3, U11.52 (PC11)
USART4_TX: AUX_SER1.2, U11.51 (PC10)
USB_DM: R4.1, USB1.D-
USB_DM_IN: R4.2, SJ1.2, SJ3.1
USB_DM_IN1: SJ3.2, U11.44 (PA11)
USB_DM_IN2: SJ1.1, U10.44 (44.PA11)
USB_DP: R5.1, USB1.D+
USB_DP_IN: R5.2, SJ2.2, SJ4.1
USB_DP_IN1: SJ4.2, U11.45 (PA12)
USB_DP_IN2: SJ2.1, U10.45 (45.PA12)
VBAT: U11.1 (VBAT)
VIN: F2.P$2, U12.3 (VIN)
VIN_PROTECTED: F2.P$1, LIPO.1, R7.2
WIFI_RESET: U10.26 (26.PB0), XBEE.5 (RESET)
WIFLY_AP: AP.2, XBEE.9 (DTR)
XTAL3: C6.1, U11.5 (PH0), X1.P$1
XTAL4: C7.1, R3.2, X1.P$2

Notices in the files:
parts and their libraries:
SparkFun-RF: Licensing: CC v3.0 Share-Alike You are welcome to use this library for commercial purposes.
